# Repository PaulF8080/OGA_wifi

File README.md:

# OGA_wifi_flex
PCB for adding wifi with a flex connector to the original Odroid Go Advance similar the new revision.

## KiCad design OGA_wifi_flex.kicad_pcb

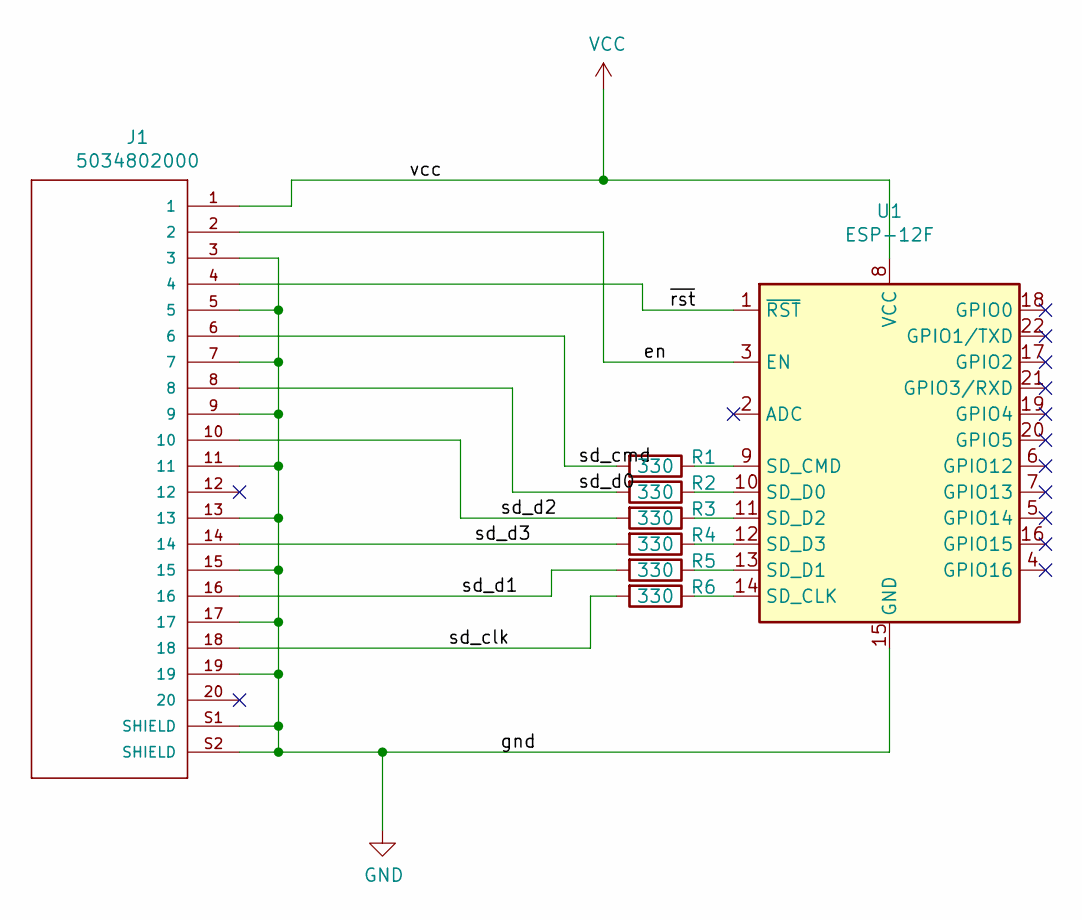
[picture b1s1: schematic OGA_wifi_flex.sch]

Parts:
J1: 5034802000; MOLEX_5034802000
R1, R2, R3, R4, R5, R6: 330; R_0805_HandSoldering
U1: ESP-12F; ESP-12E

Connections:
/en: J1.2, U1.3 (EN)
/sd_clk: J1.18, R6.2
/sd_cmd: J1.6, R1.2
/sd_d0: J1.8, R2.2
/sd_d1: J1.16, R5.2
/sd_d2: J1.10, R3.2
/sd_d3: J1.14, R4.2
/~rst: J1.4, U1.1 (~RST)
GND: J1.3, J1.5, J1.7, J1.9, J1.11, J1.13, J1.15, J1.17, J1.19, J1.S1 (SHIELD), J1.S2 (SHIELD), U1.15 (GND)
unnamed: R1.1, U1.9 (SD_CMD)
unnamed: R2.1, U1.10 (SD_D0)
unnamed: R3.1, U1.11 (SD_D2)
unnamed: R4.1, U1.12 (SD_D3)
unnamed: R5.1, U1.13 (SD_D1)
unnamed: R6.1, U1.14 (SD_CLK)
VCC: J1.1, U1.8 (VCC)

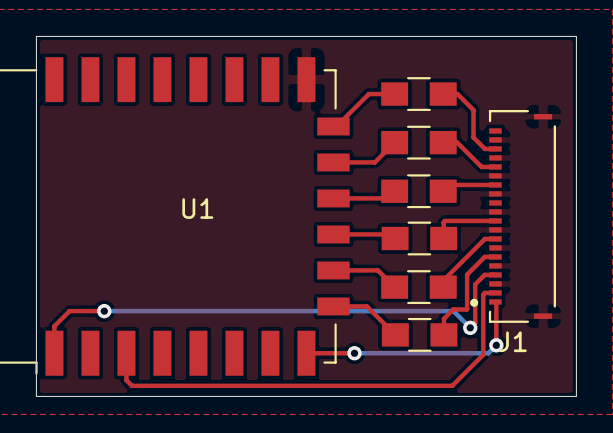
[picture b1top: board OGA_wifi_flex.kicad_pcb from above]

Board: 2 copper layers, 30.0 x 20.0 mm, 8 parts (0 on the bottom side), 16 nets.

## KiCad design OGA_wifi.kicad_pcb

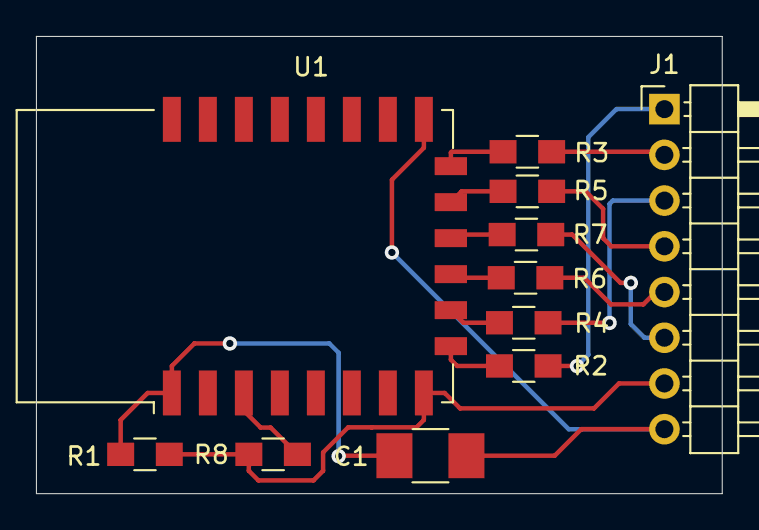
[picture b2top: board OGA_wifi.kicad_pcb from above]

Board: 2 copper layers, 38.1 x 25.4 mm, 11 parts (0 on the bottom side), 11 nets.

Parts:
C1: 0.1µF; C_1210_HandSoldering
J1: Conn_01x08; Pin_Header_Angled_1x08_Pitch2.54mm
R1: 10k; R_0805_HandSoldering
R2, R3, R4, R5, R6, R7: 33; R_0805_HandSoldering
R8: 0; R_0805_HandSoldering
U1: ESP-12F; ESP-12E

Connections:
+3V3: R1.1, R8.2, U1.8
GND: C1.2, U1.15
unnamed: C1.1, R1.2, U1.1
unnamed: J1.2, R7.2
unnamed: R2.1, U1.9
unnamed: R3.1, U1.14
unnamed: R4.1, U1.10
unnamed: R5.1, U1.13
unnamed: R6.1, U1.11
unnamed: R7.1, U1.12
unnamed: R8.1, U1.3

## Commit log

2020-06-27 Added Kicad project
2020-06-28 added gerber and drill files
2020-06-28 made gerber zip used to manufature boards
2020-06-29 rename project and changed to flex connector
2020-06-29 edit README.md
2020-06-30 different pcb and sch for this branch
2020-07-01 add signal names for ease of rotating for the two ends
